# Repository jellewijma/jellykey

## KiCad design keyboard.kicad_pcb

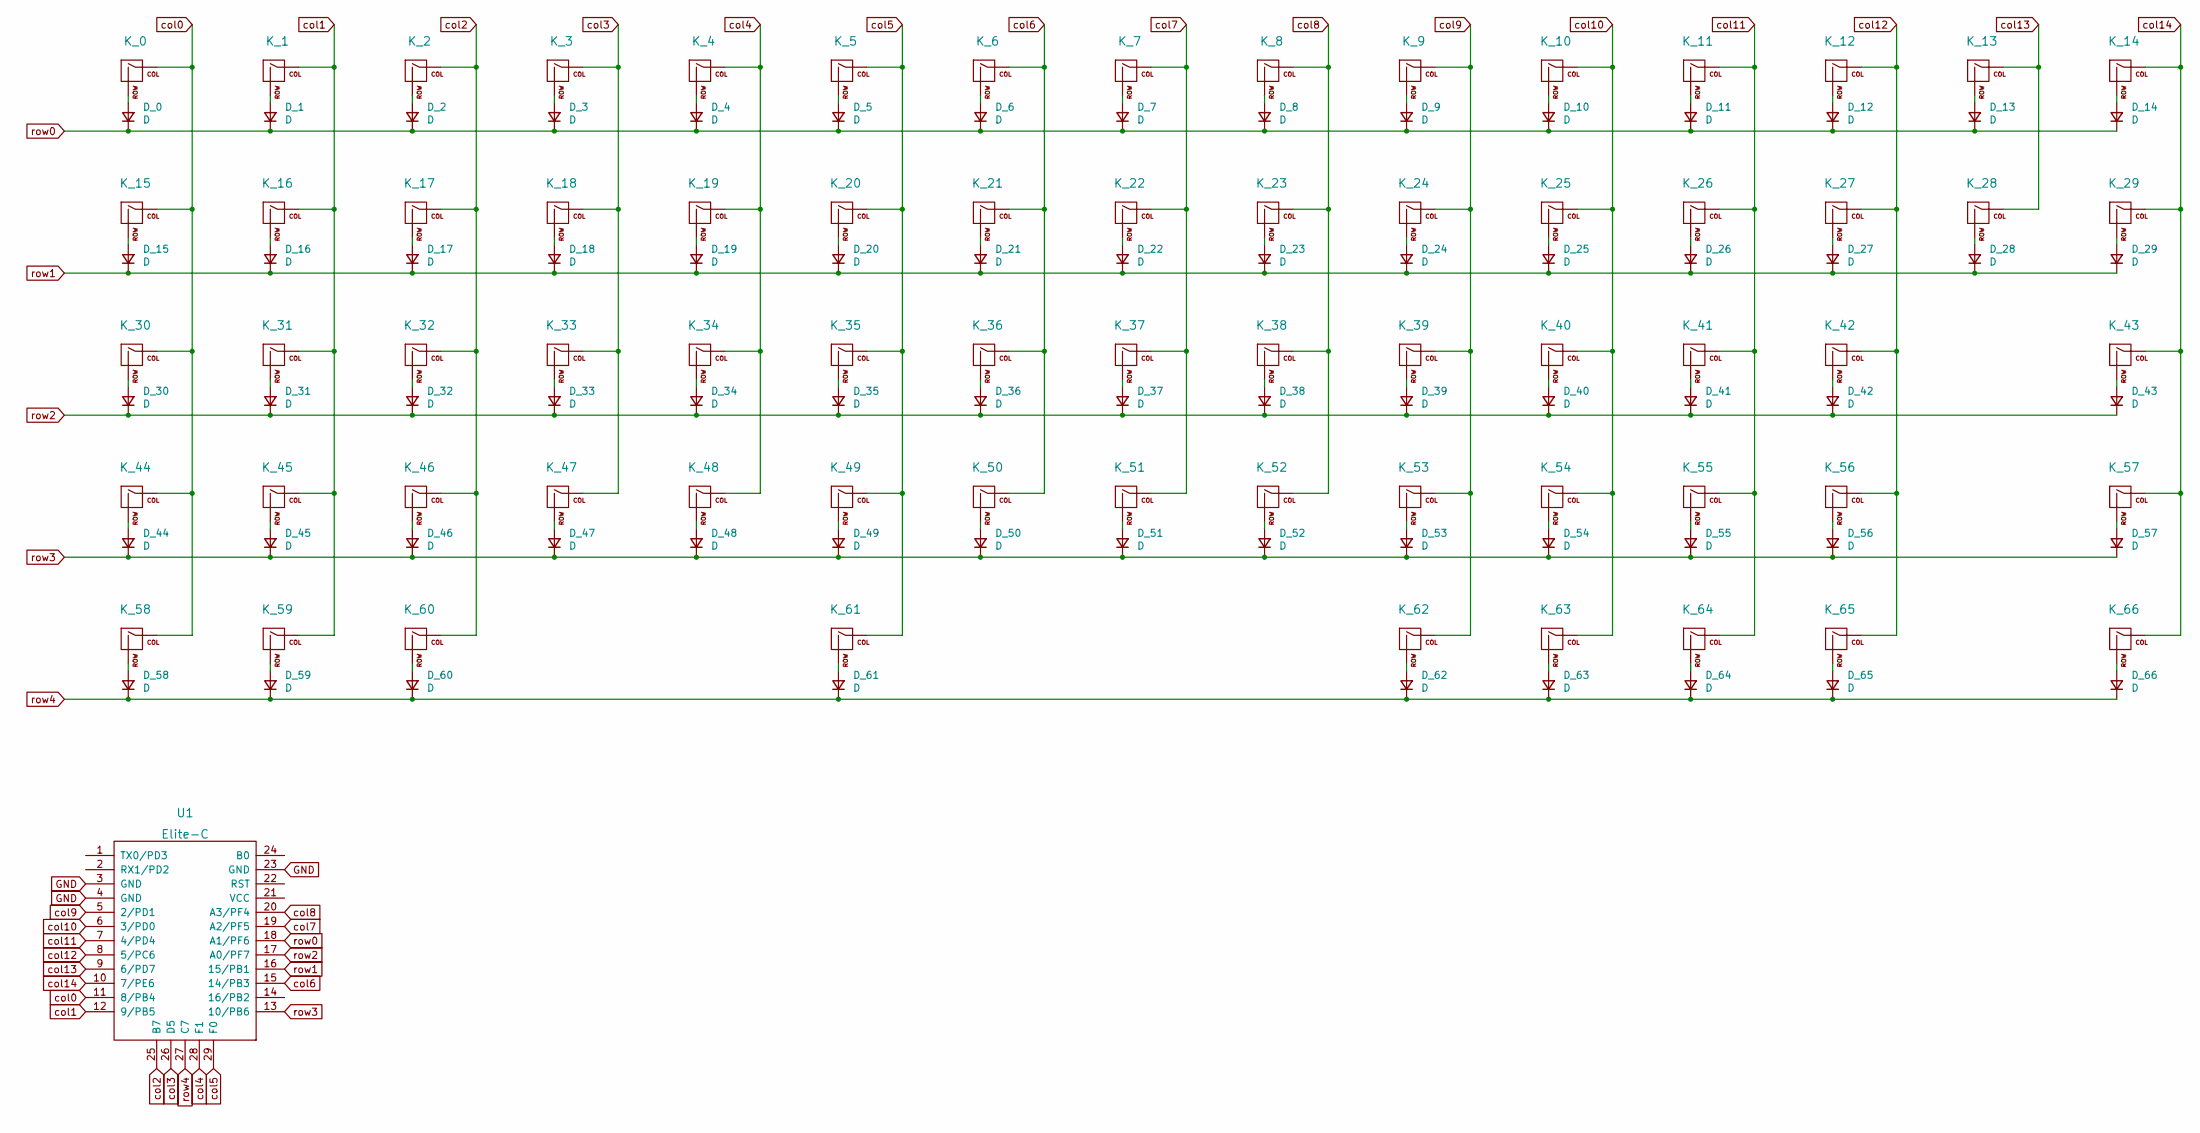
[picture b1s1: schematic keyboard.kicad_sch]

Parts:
D_0, D_1, D_2, D_3, D_4, D_5, D_6, D_7, D_8, D_9, D_10, D_11, D_12, D_13, D_14, D_15, D_16, D_17, D_18, D_19, D_20, D_21, D_22, D_23, D_24, D_25, D_26, D_27, D_28, D_29, D_30, D_31, D_32, D_33, D_34, D_35, D_36, D_37, D_38, D_39, D_40, D_41, D_42, D_43, D_44, D_45, D_46, D_47, D_48, D_49, D_50, D_51, D_52, D_53, D_54, D_55, D_56, D_57, D_58, D_59, D_60, D_61, D_62, D_63, D_64, D_65, D_66: D; D_SOD123_axial
K_0, K_1, K_2, K_3, K_4, K_5, K_6, K_7, K_8, K_9, K_10, K_11, K_12, K_13, K_14, K_15, K_16, K_17, K_18, K_19, K_20, K_21, K_22, K_23, K_24, K_25, K_26, K_27, K_28, K_29, K_30, K_31, K_32, K_33, K_34, K_35, K_36, K_37, K_38, K_39, K_40, K_41, K_42, K_43, K_44, K_45, K_46, K_47, K_48, K_49, K_50, K_51, K_52, K_53, K_54, K_55, K_56, K_57, K_58, K_59, K_60, K_61, K_62, K_63, K_64, K_65, K_66: KEYSW; KailhChoc-1U
U1: Elite-C

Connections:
GND: U1.3 (GND), U1.4 (GND), U1.23 (GND)
unnamed: D_0.2 (A), K_0.2 (ROW)
unnamed: D_1.2 (A), K_1.2 (ROW)
unnamed: D_2.2 (A), K_2.2 (ROW)
unnamed: D_3.2 (A), K_3.2 (ROW)
unnamed: D_4.2 (A), K_4.2 (ROW)
unnamed: D_5.2 (A), K_5.2 (ROW)
unnamed: D_6.2 (A), K_6.2 (ROW)
unnamed: D_7.2 (A), K_7.2 (ROW)
unnamed: D_8.2 (A), K_8.2 (ROW)
unnamed: D_9.2 (A), K_9.2 (ROW)
unnamed: D_10.2 (A), K_10.2 (ROW)
unnamed: D_11.2 (A), K_11.2 (ROW)
unnamed: D_12.2 (A), K_12.2 (ROW)
unnamed: D_13.2 (A), K_13.2 (ROW)
unnamed: D_14.2 (A), K_14.2 (ROW)
unnamed: D_15.2 (A), K_15.2 (ROW)
unnamed: D_16.2 (A), K_16.2 (ROW)
unnamed: D_17.2 (A), K_17.2 (ROW)
unnamed: D_18.2 (A), K_18.2 (ROW)
unnamed: D_19.2 (A), K_19.2 (ROW)
unnamed: D_20.2 (A), K_20.2 (ROW)
unnamed: D_21.2 (A), K_21.2 (ROW)
unnamed: D_22.2 (A), K_22.2 (ROW)
unnamed: D_23.2 (A), K_23.2 (ROW)
unnamed: D_24.2 (A), K_24.2 (ROW)
unnamed: D_25.2 (A), K_25.2 (ROW)
unnamed: D_26.2 (A), K_26.2 (ROW)
unnamed: D_27.2 (A), K_27.2 (ROW)
unnamed: D_28.2 (A), K_28.2 (ROW)
unnamed: D_29.2 (A), K_29.2 (ROW)
unnamed: D_30.2 (A), K_30.2 (ROW)
unnamed: D_31.2 (A), K_31.2 (ROW)
unnamed: D_32.2 (A), K_32.2 (ROW)
unnamed: D_33.2 (A), K_33.2 (ROW)
unnamed: D_34.2 (A), K_34.2 (ROW)
unnamed: D_35.2 (A), K_35.2 (ROW)
unnamed: D_36.2 (A), K_36.2 (ROW)
unnamed: D_37.2 (A), K_37.2 (ROW)
unnamed: D_38.2 (A), K_38.2 (ROW)
unnamed: D_39.2 (A), K_39.2 (ROW)
unnamed: D_40.2 (A), K_40.2 (ROW)
unnamed: D_41.2 (A), K_41.2 (ROW)
unnamed: D_42.2 (A), K_42.2 (ROW)
unnamed: D_43.2 (A), K_43.2 (ROW)
unnamed: D_44.2 (A), K_44.2 (ROW)
unnamed: D_45.2 (A), K_45.2 (ROW)
unnamed: D_46.2 (A), K_46.2 (ROW)
unnamed: D_47.2 (A), K_47.2 (ROW)
unnamed: D_48.2 (A), K_48.2 (ROW)
unnamed: D_49.2 (A), K_49.2 (ROW)
unnamed: D_50.2 (A), K_50.2 (ROW)
unnamed: D_51.2 (A), K_51.2 (ROW)
unnamed: D_52.2 (A), K_52.2 (ROW)
unnamed: D_53.2 (A), K_53.2 (ROW)
unnamed: D_54.2 (A), K_54.2 (ROW)
unnamed: D_55.2 (A), K_55.2 (ROW)
unnamed: D_56.2 (A), K_56.2 (ROW)
unnamed: D_57.2 (A), K_57.2 (ROW)
unnamed: D_58.2 (A), K_58.2 (ROW)
unnamed: D_59.2 (A), K_59.2 (ROW)
unnamed: D_60.2 (A), K_60.2 (ROW)
unnamed: D_61.2 (A), K_61.2 (ROW)
unnamed: D_62.2 (A), K_62.2 (ROW)
unnamed: D_63.2 (A), K_63.2 (ROW)
unnamed: D_64.2 (A), K_64.2 (ROW)
unnamed: D_65.2 (A), K_65.2 (ROW)
unnamed: D_66.2 (A), K_66.2 (ROW)
col0: K_0.1 (COL), K_15.1 (COL), K_30.1 (COL), K_44.1 (COL), K_58.1 (COL), U1.11 (8/PB4)
col1: K_1.1 (COL), K_16.1 (COL), K_31.1 (COL), K_45.1 (COL), K_59.1 (COL), U1.12 (9/PB5)
col2: K_2.1 (COL), K_17.1 (COL), K_32.1 (COL), K_46.1 (COL), K_60.1 (COL), U1.25 (B7)
col3: K_3.1 (COL), K_18.1 (COL), K_33.1 (COL), K_47.1 (COL), U1.26 (D5)
col4: K_4.1 (COL), K_19.1 (COL), K_34.1 (COL), K_48.1 (COL), U1.28 (F1)
col5: K_5.1 (COL), K_20.1 (COL), K_35.1 (COL), K_49.1 (COL), K_61.1 (COL), U1.29 (F0)
col6: K_6.1 (COL), K_21.1 (COL), K_36.1 (COL), K_50.1 (COL), U1.15 (14/PB3)
col7: K_7.1 (COL), K_22.1 (COL), K_37.1 (COL), K_51.1 (COL), U1.19 (A2/PF5)
col8: K_8.1 (COL), K_23.1 (COL), K_38.1 (COL), K_52.1 (COL), U1.20 (A3/PF4)
col9: K_9.1 (COL), K_24.1 (COL), K_39.1 (COL), K_53.1 (COL), K_62.1 (COL), U1.5 (2/PD1)
col10: K_10.1 (COL), K_25.1 (COL), K_40.1 (COL), K_54.1 (COL), K_63.1 (COL), U1.6 (3/PD0)
col11: K_11.1 (COL), K_26.1 (COL), K_41.1 (COL), K_55.1 (COL), K_64.1 (COL), U1.7 (4/PD4)
col12: K_12.1 (COL), K_27.1 (COL), K_42.1 (COL), K_56.1 (COL), K_65.1 (COL), U1.8 (5/PC6)
col13: K_13.1 (COL), K_28.1 (COL), U1.9 (6/PD7)
col14: K_14.1 (COL), K_29.1 (COL), K_43.1 (COL), K_57.1 (COL), K_66.1 (COL), U1.10 (7/PE6)
row0: D_0.1 (K), D_1.1 (K), D_2.1 (K), D_3.1 (K), D_4.1 (K), D_5.1 (K), D_6.1 (K), D_7.1 (K), D_8.1 (K), D_9.1 (K), D_10.1 (K), D_11.1 (K), D_12.1 (K), D_13.1 (K), D_14.1 (K), U1.18 (A1/PF6)
row1: D_15.1 (K), D_16.1 (K), D_17.1 (K), D_18.1 (K), D_19.1 (K), D_20.1 (K), D_21.1 (K), D_22.1 (K), D_23.1 (K), D_24.1 (K), D_25.1 (K), D_26.1 (K), D_27.1 (K), D_28.1 (K), D_29.1 (K), U1.16 (15/PB1)
row2: D_30.1 (K), D_31.1 (K), D_32.1 (K), D_33.1 (K), D_34.1 (K), D_35.1 (K), D_36.1 (K), D_37.1 (K), D_38.1 (K), D_39.1 (K), D_40.1 (K), D_41.1 (K), D_42.1 (K), D_43.1 (K), U1.17 (A0/PF7)
row3: D_44.1 (K), D_45.1 (K), D_46.1 (K), D_47.1 (K), D_48.1 (K), D_49.1 (K), D_50.1 (K), D_51.1 (K), D_52.1 (K), D_53.1 (K), D_54.1 (K), D_55.1 (K), D_56.1 (K), D_57.1 (K), U1.13 (10/PB6)
row4: D_58.1 (K), D_59.1 (K), D_60.1 (K), D_61.1 (K), D_62.1 (K), D_63.1 (K), D_64.1 (K), D_65.1 (K), D_66.1 (K), U1.27 (C7)

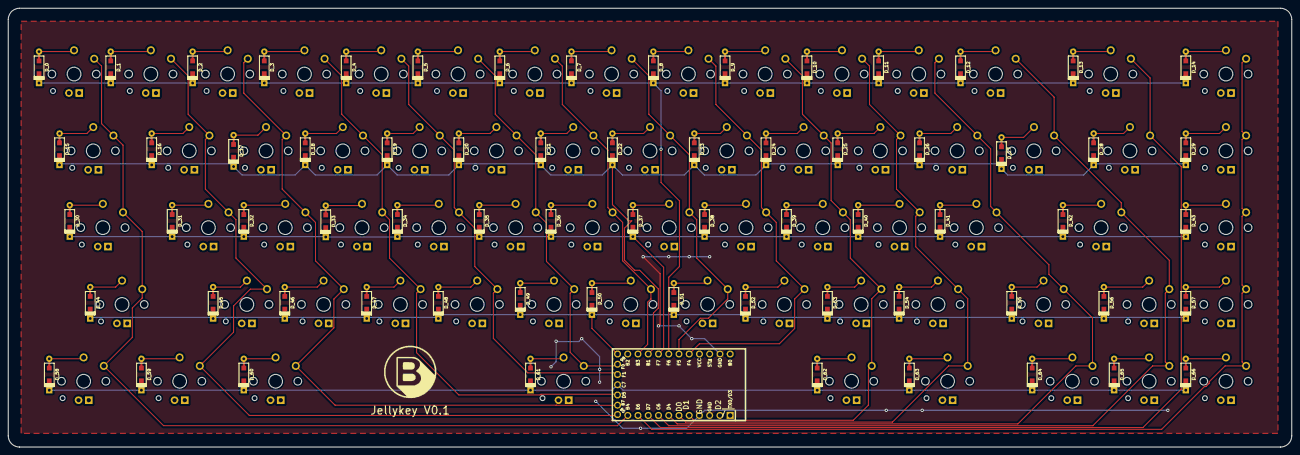
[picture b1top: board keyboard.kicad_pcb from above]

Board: 2 copper layers, 318.4 x 108.8 mm, 135 parts (1 on the bottom side), 88 nets.

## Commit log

2023-02-02 files added
